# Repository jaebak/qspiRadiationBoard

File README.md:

KiCad project for a qspi radiation test board

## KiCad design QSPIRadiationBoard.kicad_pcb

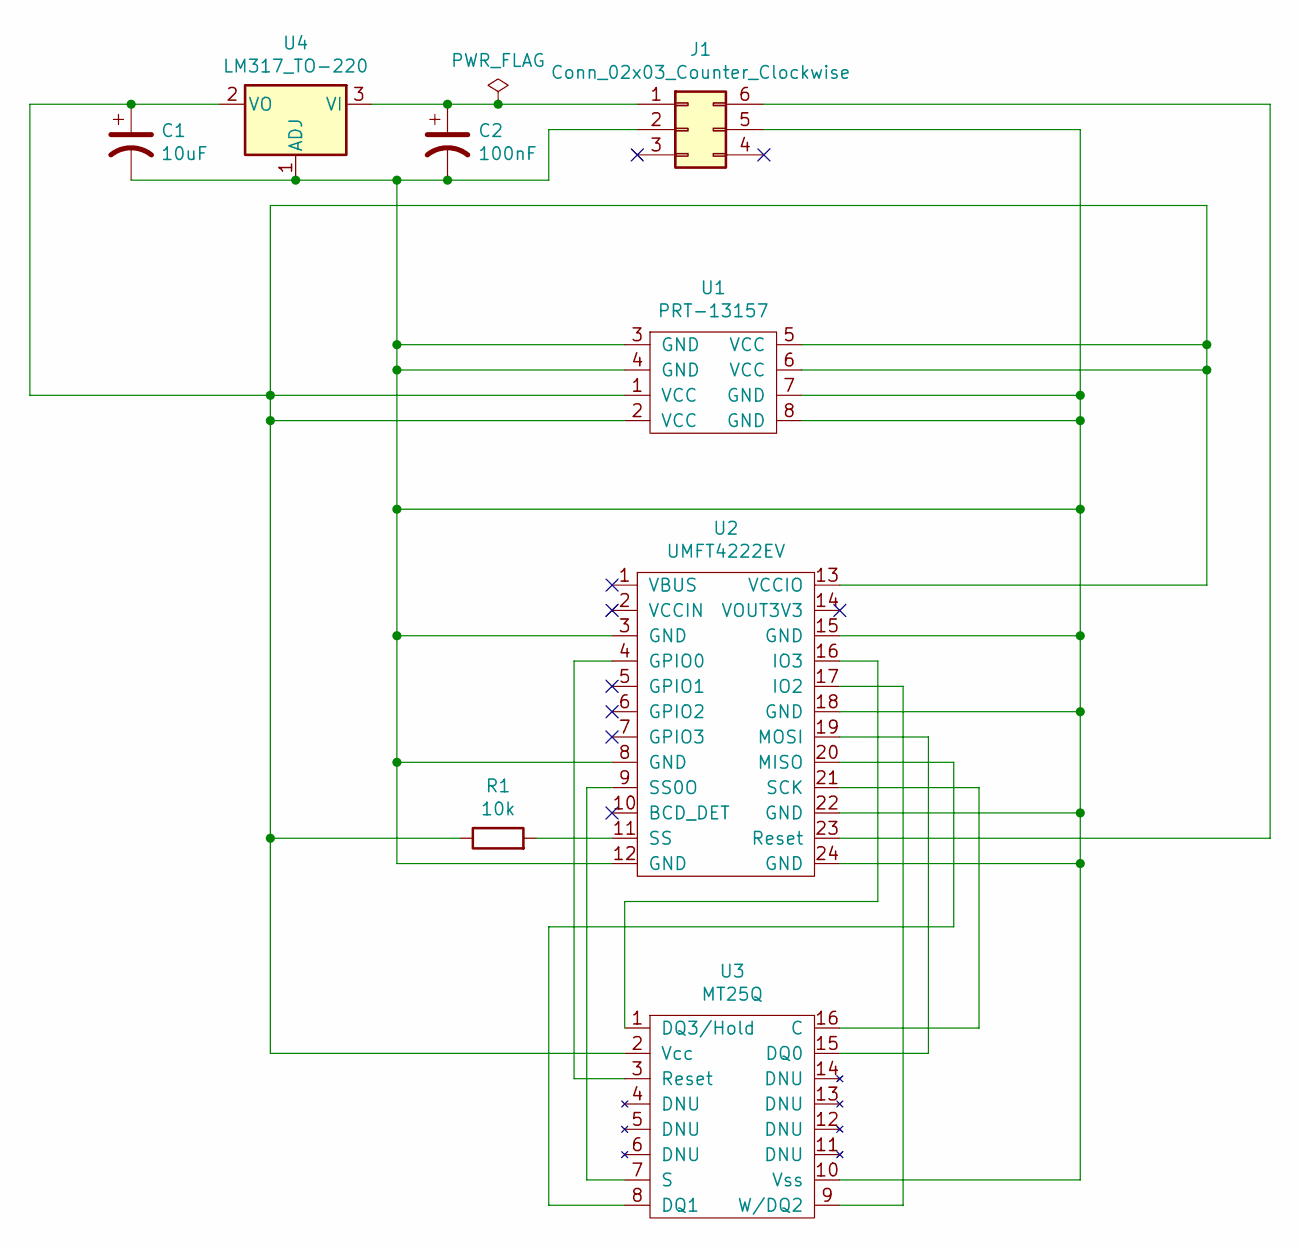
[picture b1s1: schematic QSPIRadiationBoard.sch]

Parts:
C1: 10uF; CP_Radial_Tantal_D4.5mm_P2.50mm
C2: 100nF; CP_Radial_Tantal_D4.5mm_P2.50mm
J1: Conn_02x03_Counter_Clockwise; molex_39-30-1061
R1: 10k; R_Axial_DIN0207_L6.3mm_D2.5mm_P7.62mm_Horizontal
U1: PRT-13157
U2: UMFT4222EV
U3: MT25Q
U4: LM317_TO-220; TO-220-3_Vertical

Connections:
unnamed: C1.1, R1.1, U1.1 (VCC), U1.2 (VCC), U1.5 (VCC), U1.6 (VCC), U2.13 (VCCIO), U3.2 (Vcc), U4.2 (VO)
unnamed: C1.2, C2.2, J1.2, J1.5, U1.3 (GND), U1.4 (GND), U1.7 (GND), U1.8 (GND), U2.3 (GND), U2.8 (GND), U2.12 (GND), U2.15 (GND), U2.18 (GND), U2.22 (GND), U2.24 (GND), U3.10 (Vss), U4.1 (ADJ)
unnamed: C2.1, J1.1, U4.3 (VI)
unnamed: J1.6, U2.23 (Reset)
unnamed: R1.2, U2.11 (SS)
unnamed: U2.4 (GPIO0), U3.3 (Reset)
unnamed: U2.9 (SS0O), U3.7 (S)
unnamed: U2.16 (IO3), U3.1 (DQ3/Hold)
unnamed: U2.17 (IO2), U3.9 (W/DQ2)
unnamed: U2.19 (MOSI), U3.15 (DQ0)
unnamed: U2.20 (MISO), U3.8 (DQ1)
unnamed: U2.21 (SCK), U3.16 (C)

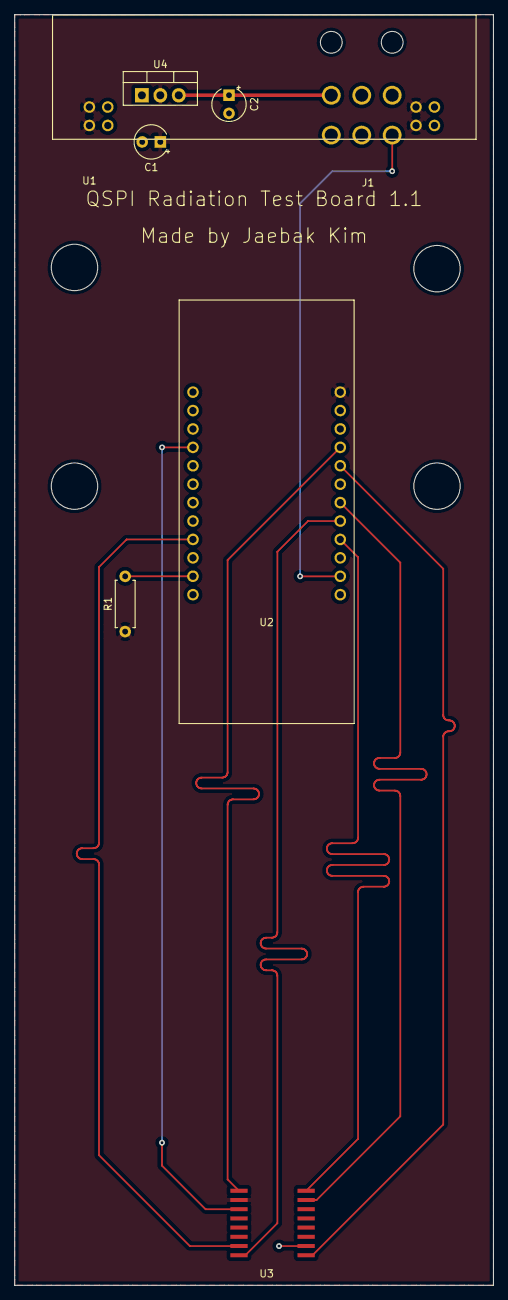
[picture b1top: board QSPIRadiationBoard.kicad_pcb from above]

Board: 2 copper layers, 66.0 x 175.3 mm, 8 parts (0 on the bottom side), 12 nets.

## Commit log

2020-07-01 Added readme
